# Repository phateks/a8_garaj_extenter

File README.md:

# Kincony A8 - 14 Inputs Extender 

> **_NOTE:_**  **The address of the MCP is fixed to 0x20**

**BOM is not created in the files**

3v3 - TSR2-2433N - TracoPower

For TCMT1100 Anod connection i used 1.8K Ohm with 12VDC input - 0805

For TCMT1100 Emitter connection i used 4.7K Ohm for pullup on 3v3. - 0805

Capacitor 100nF - 1026

2 x Connector 1x7 - 1823683 - PhoenixContact

> **_NOTE:_**  **There are no I2C resistors on the board, if this is used for somethig else they must be placed somewhere else if needed**

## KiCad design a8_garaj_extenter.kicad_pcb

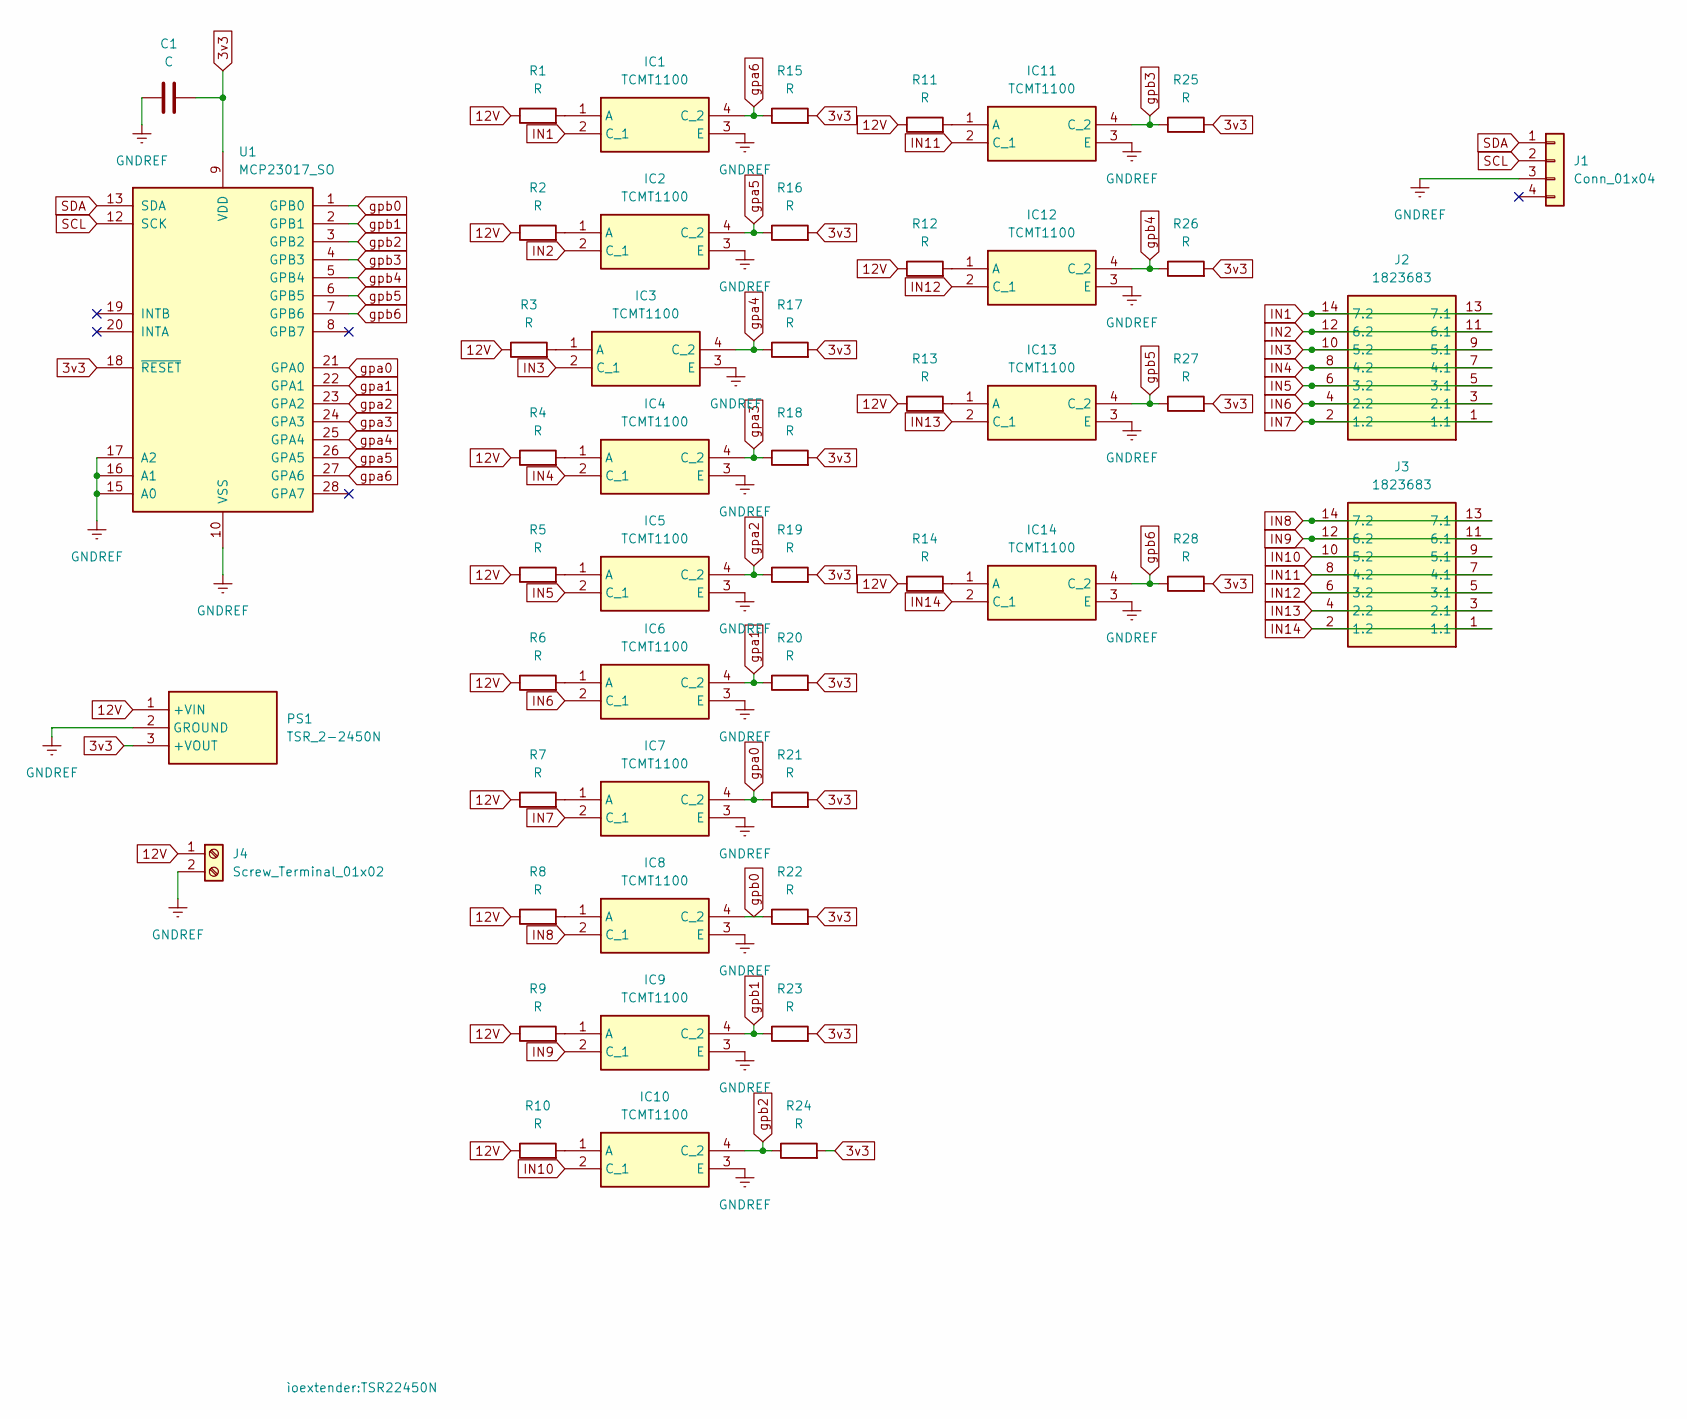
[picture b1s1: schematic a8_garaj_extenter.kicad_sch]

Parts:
C1: C; C_1206_3216Metric_Pad1.33x1.80mm_HandSolder
IC1, IC2, IC3, IC4, IC5, IC6, IC7, IC8, IC9, IC10, IC11, IC12, IC13, IC14: TCMT1100; opto_tcmt1100; Manufacturer_Part_Number TCMT1100; Mouser Part Number 782-TCMT1100
J1: Conn_01x04; JST_XA_B04B-XASK-1_1x04_P2.50mm_Vertical
J2, J3: 1823683; Manufacturer_Part_Number 1823683; Mouser Part Number 651-1823683
J4: Screw_Terminal_01x02; TerminalBlock_MetzConnect_Type059_RT06302HBWC_1x02_P3.50mm_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
PS1: TSR_2-2450N; TSR22450N; Manufacturer_Part_Number TSR 2-2450N; Mouser Part Number 495-TSR2-2450N
R1, R2, R3, R4, R5, R6, R7, R8, R9, R10, R11, R12, R13, R14, R15, R16, R17, R18, R19, R20, R21, R22, R23, R24, R25, R26, R27, R28: R; R_0805_2012Metric_Pad1.20x1.40mm_HandSolder
U1: MCP23017_SO; SOIC-28W_7.5x17.9mm_P1.27mm

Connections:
3v3: C1.2, PS1.3 (+VOUT), R15.2, R16.2, R17.2, R18.2, R19.2, R20.2, R21.2, R22.2, R23.2, R24.2, R25.2, R26.2, R27.2, R28.2, U1.9 (VDD), U1.18 (~RESET)
12V: J4.1, PS1.1 (+VIN), R1.1, R2.1, R3.1, R4.1, R5.1, R6.1, R7.1, R8.1, R9.1, R10.1, R11.1, R12.1, R13.1, R14.1
GNDREF: C1.1, IC1.3 (E), IC2.3 (E), IC3.3 (E), IC4.3 (E), IC5.3 (E), IC6.3 (E), IC7.3 (E), IC8.3 (E), IC9.3 (E), IC10.3 (E), IC11.3 (E), IC12.3 (E), IC13.3 (E), IC14.3 (E), J1.3, J4.2, PS1.2 (GROUND), U1.10 (VSS), U1.15 (A0), U1.16 (A1), U1.17 (A2)
IN1: IC1.2 (C_1), J2.13 (7.1), J2.14 (7.2)
IN2: IC2.2 (C_1), J2.11 (6.1), J2.12 (6.2)
IN3: IC3.2 (C_1), J2.9 (5.1), J2.10 (5.2)
IN4: IC4.2 (C_1), J2.7 (4.1), J2.8 (4.2)
IN5: IC5.2 (C_1), J2.5 (3.1), J2.6 (3.2)
IN6: IC6.2 (C_1), J2.3 (2.1), J2.4 (2.2)
IN7: IC7.2 (C_1), J2.1 (1.1), J2.2 (1.2)
IN8: IC8.2 (C_1), J3.13 (7.1), J3.14 (7.2)
IN9: IC9.2 (C_1), J3.11 (6.1), J3.12 (6.2)
IN10: IC10.2 (C_1), J3.9 (5.1), J3.10 (5.2)
IN11: IC11.2 (C_1), J3.7 (4.1), J3.8 (4.2)
IN12: IC12.2 (C_1), J3.5 (3.1), J3.6 (3.2)
IN13: IC13.2 (C_1), J3.3 (2.1), J3.4 (2.2)
IN14: IC14.2 (C_1), J3.1 (1.1), J3.2 (1.2)
unnamed: IC1.1 (A), R1.2
unnamed: IC2.1 (A), R2.2
unnamed: IC3.1 (A), R3.2
unnamed: IC4.1 (A), R4.2
unnamed: IC5.1 (A), R5.2
unnamed: IC6.1 (A), R6.2
unnamed: IC7.1 (A), R7.2
unnamed: IC8.1 (A), R8.2
unnamed: IC9.1 (A), R9.2
unnamed: IC10.1 (A), R10.2
unnamed: IC11.1 (A), R11.2
unnamed: IC12.1 (A), R12.2
unnamed: IC13.1 (A), R13.2
unnamed: IC14.1 (A), R14.2
SCL: J1.2, U1.12 (SCK)
SDA: J1.1, U1.13 (SDA)
gpa0: IC7.4 (C_2), R21.1, U1.21 (GPA0)
gpa1: IC6.4 (C_2), R20.1, U1.22 (GPA1)
gpa2: IC5.4 (C_2), R19.1, U1.23 (GPA2)
gpa3: IC4.4 (C_2), R18.1, U1.24 (GPA3)
gpa4: IC3.4 (C_2), R17.1, U1.25 (GPA4)
gpa5: IC2.4 (C_2), R16.1, U1.26 (GPA5)
gpa6: IC1.4 (C_2), R15.1, U1.27 (GPA6)
gpb0: IC8.4 (C_2), R22.1, U1.1 (GPB0)
gpb1: IC9.4 (C_2), R23.1, U1.2 (GPB1)
gpb2: IC10.4 (C_2), R24.1, U1.3 (GPB2)
gpb3: IC11.4 (C_2), R25.1, U1.4 (GPB3)
gpb4: IC12.4 (C_2), R26.1, U1.5 (GPB4)
gpb5: IC13.4 (C_2), R27.1, U1.6 (GPB5)
gpb6: IC14.4 (C_2), R28.1, U1.7 (GPB6)

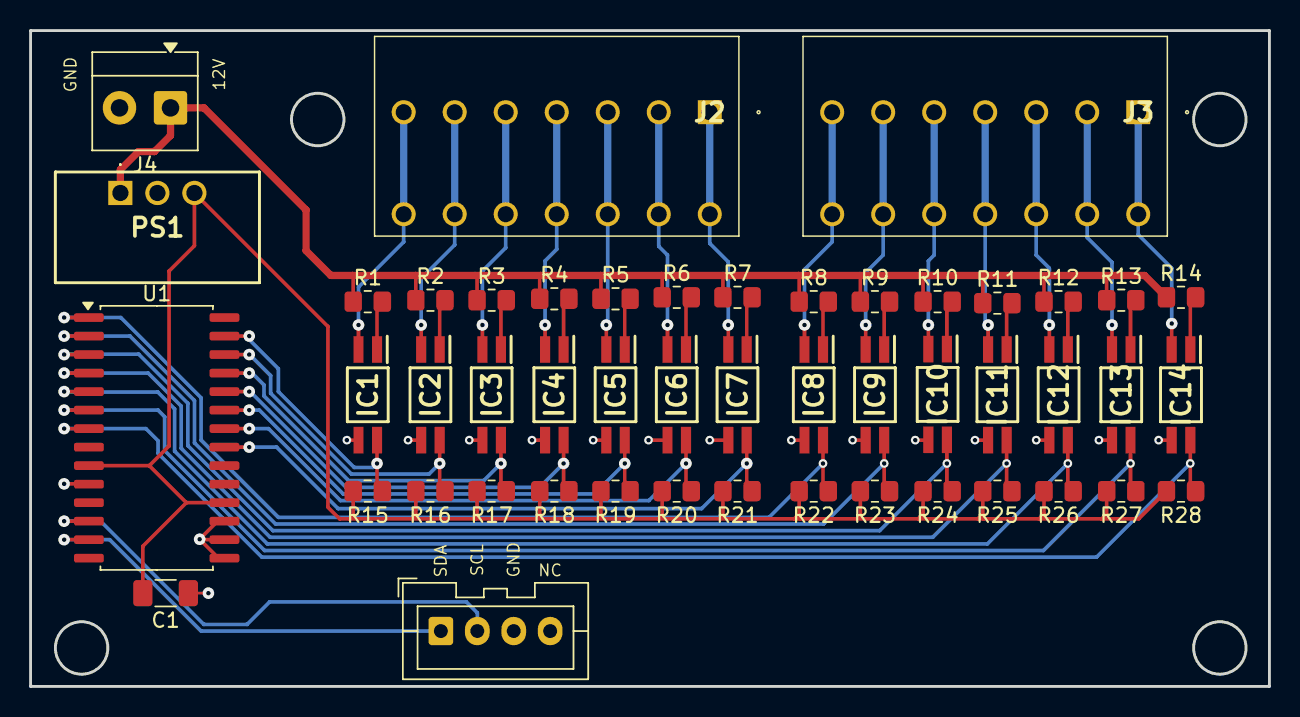
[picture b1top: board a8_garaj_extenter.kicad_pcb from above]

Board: 2 copper layers, 85.0 x 45.0 mm, 49 parts (0 on the bottom side), 47 nets.

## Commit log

2025-11-14 Revise README for Kincony A8 Inputs Extender
    Updated README with detailed information about the Kincony A8 inputs extender, including notes on components and connections.
